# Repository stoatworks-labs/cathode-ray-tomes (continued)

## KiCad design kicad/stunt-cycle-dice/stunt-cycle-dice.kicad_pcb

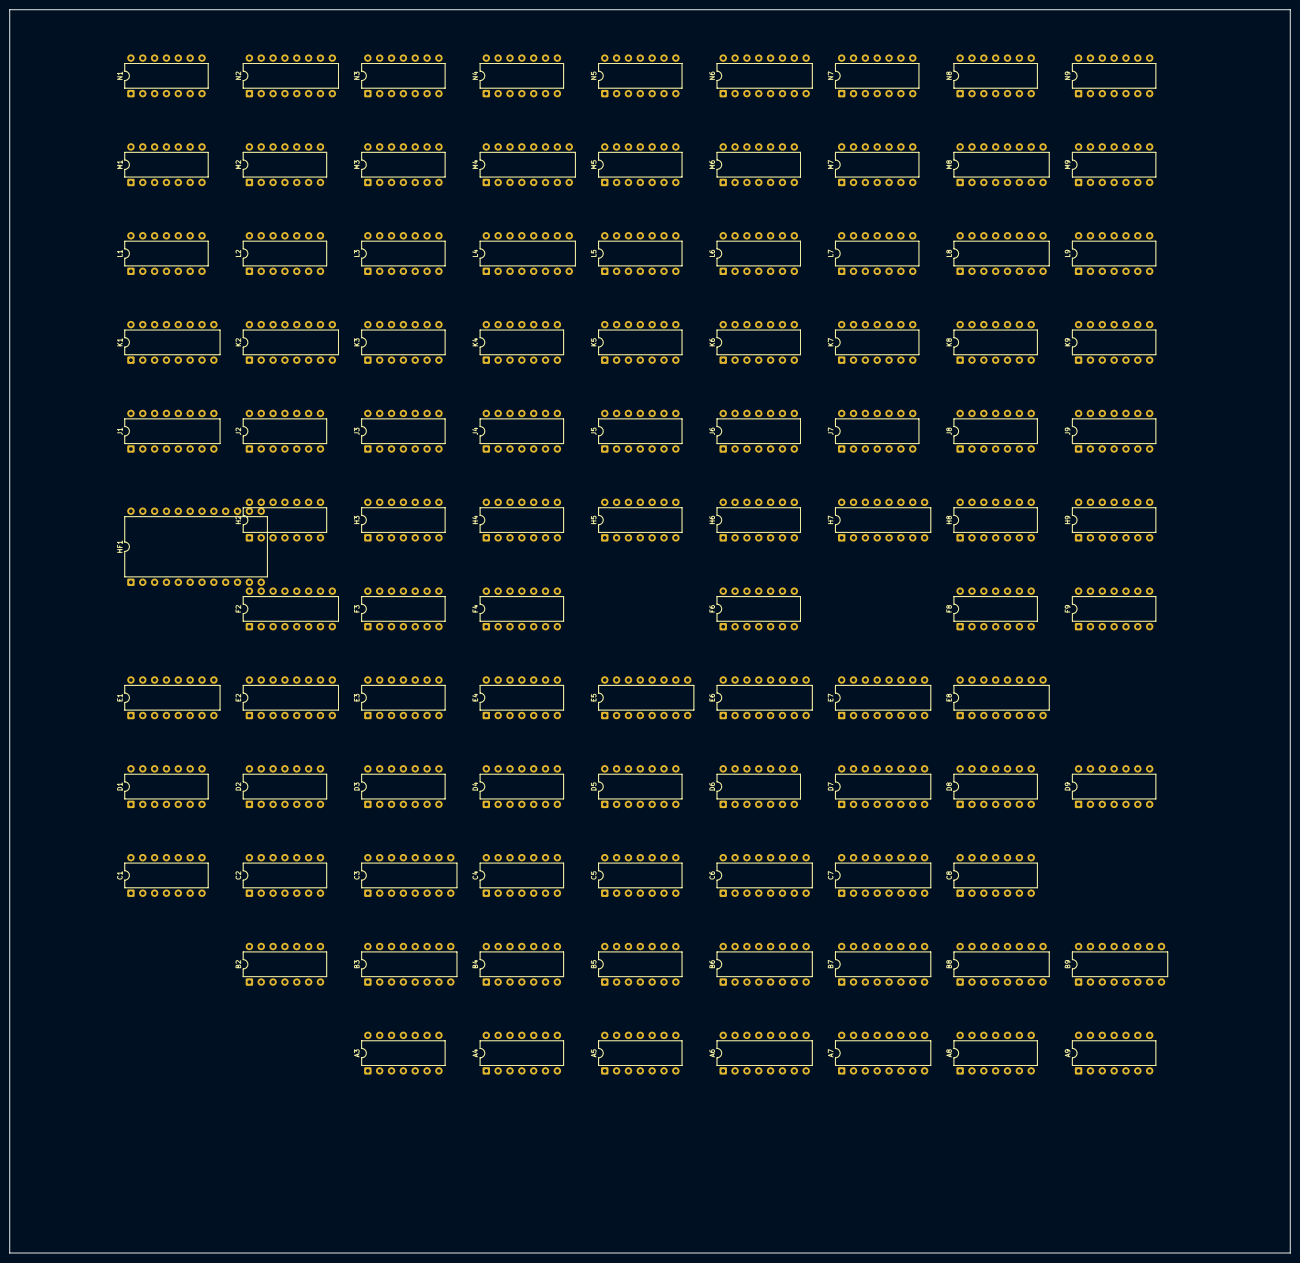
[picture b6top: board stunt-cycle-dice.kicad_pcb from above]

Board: 2 copper layers, 274.6 x 266.6 mm, 100 parts (0 on the bottom side), 328 nets, no tracks yet.

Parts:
A3: 7400; DIP-14_W7.62mm
A4, A5, A9: 7474; DIP-14_W7.62mm
A6: 9312; DIP-16_W7.62mm
A7: 9322; DIP-16_W7.62mm
A8: 7402; DIP-14_W7.62mm
B2: 7400; DIP-14_W7.62mm
B3: 9316; DIP-16_W7.62mm
B4: 74107; DIP-14_W7.62mm
B5: 7408; DIP-14_W7.62mm
B6: 9312; DIP-16_W7.62mm
B7: 9322; DIP-16_W7.62mm
B8, B9: 74192; DIP-16_W7.62mm
C1: 7493; DIP-14_W7.62mm
C2, C5: 7474; DIP-14_W7.62mm
C3: 9316; DIP-16_W7.62mm
C4: 7410; DIP-14_W7.62mm
C6: 7448; DIP-16_W7.62mm
C7: 9322; DIP-16_W7.62mm
C8: 7486; DIP-14_W7.62mm
D1: 7450; DIP-14_W7.62mm
D2, D9: 7474; DIP-14_W7.62mm
D3: 7404; DIP-14_W7.62mm
D4: 7402; DIP-14_W7.62mm
D5: 7400; DIP-14_W7.62mm
D6: 7410; DIP-14_W7.62mm
D7: 82S123; DIP-16_W7.62mm
D8: 7427; DIP-14_W7.62mm
E1, E2: 74194; DIP-16_W7.62mm
E3: 7410; DIP-14_W7.62mm
E4: 7427; DIP-14_W7.62mm
E5, E8: 74193; DIP-16_W7.62mm
E6, E7: 7485; DIP-16_W7.62mm
F2: 74165; DIP-16_W7.62mm
F3: 7450; DIP-14_W7.62mm
F4: 7400; DIP-14_W7.62mm
F6, F8: 7474; DIP-14_W7.62mm
F9: 7402; DIP-14_W7.62mm
H2: 7400; DIP-14_W7.62mm
H3, H8: 7474; DIP-14_W7.62mm
H4, H9: 7410; DIP-14_W7.62mm
H5: 7408; DIP-14_W7.62mm
H6: 7404; DIP-14_W7.62mm
H7: 9316; DIP-16_W7.62mm
HF1: 82S115; DIP-24_W15.24mm
J1: 9322; DIP-16_W7.62mm
J2, J7: 7474; DIP-14_W7.62mm
J3, J5: 7402; DIP-14_W7.62mm
J4: 7486; DIP-14_W7.62mm
J6: 7420; DIP-14_W7.62mm
J8: 7400; DIP-14_W7.62mm
J9: 74107; DIP-14_W7.62mm
K1, K2: 9316; DIP-16_W7.62mm
K3: 7493; DIP-14_W7.62mm
K4: 74107; DIP-14_W7.62mm
K5: 7427; DIP-14_W7.62mm
K6: 7402; DIP-14_W7.62mm
K7: 7474; DIP-14_W7.62mm
K8: 7404; DIP-14_W7.62mm
K9: 7450; DIP-14_W7.62mm
L1, L7: 7402; DIP-14_W7.62mm
L2, L9: 7400; DIP-14_W7.62mm
L3, L5: 7493; DIP-14_W7.62mm
L4: 9316; DIP-16_W7.62mm
L6: 7408; DIP-14_W7.62mm
L8: 74193; DIP-16_W7.62mm
M1, M3: 7474; DIP-14_W7.62mm
M2: 7486; DIP-14_W7.62mm
M4: 9316; DIP-16_W7.62mm
M5: 7410; DIP-14_W7.62mm
M6, M7: 7400; DIP-14_W7.62mm
M8: 74193; DIP-16_W7.62mm
M9: 7420; DIP-14_W7.62mm
N1: 7493; DIP-14_W7.62mm
N2: 7485; DIP-16_W7.62mm
N3: 7404; DIP-14_W7.62mm
N4, N7: 7474; DIP-14_W7.62mm
N5, N9: 7400; DIP-14_W7.62mm
N6: 9602; DIP-16_W7.62mm
N8: 7408; DIP-14_W7.62mm

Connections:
+5V: A3.14, A4.14, A5.14, A6.16, A7.16, A8.14, A9.14, B2.14, B3.16, B4.14, B5.14, B6.16, B7.16, B8.16, B9.16, C1.5, C2.14, C3.16, C4.14, C5.14, C6.16, C7.16, C8.14, D2.14, D3.14, D4.14, D5.14, D6.14, D7.16, D8.14, D9.14, E1.16, E2.16, E3.14, E4.14, E5.16, E6.16, E7.16, E8.16, F2.16, F4.14, F6.14, F8.14, F9.14, H2.14, H3.14, H4.14, H5.14, H6.14, H7.16, H8.14, H9.14, J1.16, J2.14, J3.14, J4.14, J5.14, J6.14, J7.14, J8.14, J9.14, K1.16, K2.16, K3.5, K4.14, K5.14, K6.14, K7.14, K8.14, L1.14, L2.14, L3.5, L4.16, L5.5, L6.14, L7.14, L8.16, L9.14, M1.14, M2.14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
A3-1: A3.1, C4.6
A3-3: A3.3, C4.3, C5.3
A3-4: A3.4, D3.12
A3-5: A3.5, B3.7, C3.15
A3-6: A3.6, B3.9, C2.11, C3.9
A4-8: A4.8, A8.12
A5-2: A5.2, B5.11
A5-6: A5.6, M7.5
A5-8: A5.8, J7.2
A5-11: A5.11, H5.2, H5.10, H6.1, H7.15, J7.13
A6-1: A6.1, C6.13
A6-4: A6.4, C6.14
A6-9: A6.9, C6.10
A6-14: A6.14, B5.12
A7-1: A7.1, B7.1, D1.8
A7-2: A7.2, A8.8, A9.9
A7-3: A7.3, A8.2, A9.5
A7-4: A7.4, C7.2, D7.14
A7-5: A7.5, A8.10
A7-6: A7.6, A8.1
A7-7: A7.7, C7.5
A8-3: A8.3, B7.10, B9.7
A8-4: A8.4, B8.5
A8-5: A8.5, B5.4, D5.12, D6.9, E5.3
A8-6: A8.6, C5.8
A8-9: A8.9, B7.11, B8.7
A8-13: A8.13, D3.9
A9-2: A9.2, A9.6
A9-3: A9.3, B9.12
A9-8: A9.8, A9.12
A9-11: A9.11, B8.12
ATTRACT: D9.8, D9.10, F3.2, F8.3, H8.3
ATTRACT_n: D8.13, D9.9, F3.1, F8.13, H5.12, H9.9, M5.4
B2-2: B2.2, B2.13, D3.8
B2-5: B2.5, C2.9, C3.3
B2-6: B2.6, C3.4
B3-15: B3.15, B4.9, C4.2
B4-2: B4.2, C4.1
B4-3: B4.3, C4.11
B4-5: B4.5, B4.12, C4.9, C4.13
B5-2: B5.2, B5.8, E4.1
B5-3: B5.3, D4.12
B5-5: B5.5, C5.9
B5-6: B5.6, B9.5
B5-13: B5.13, B6.14
B6-1: B6.1, C6.15
B6-4: B6.4, C6.12
B6-5: B6.5, C6.9
B6-9: B6.9, C6.11
B7-2: B7.2, B8.3
B7-3: B7.3, B9.3
B7-4: B7.4, C7.3, D7.10
B7-5: B7.5, B8.2
B7-6: B7.6, B9.2
B7-7: B7.7, C7.6, D7.11
B7-9: B7.9, C7.10, D7.13
B7-12: B7.12, C7.13, D7.12
B7-13: B7.13, B9.6
B7-14: B7.14, B8.6
BAD_JUMP: K7.9, L7.2, L7.12, L9.4, N6.4
BAD_JUMP_n: C4.4, F6.13, J7.1, K7.8, L9.2, L9.12, M7.10, M9.4, N9.9
C1-1: C1.1, C1.12
C1-14: C1.14, C2.5, C2.12
C2-1: C2.1, C2.8
C4-8: C4.8, E4.13
C4-12: C4.12, D3.13
C5-1: C5.1, D6.8
C5-6: C5.6, K6.8
C5-12: C5.12, D7.6, K6.5
C5-13: C5.13, H5.11
C6-1: C6.1, C7.7
C6-2: C6.2, C7.12
C6-6: C6.6, C7.9
C6-7: C6.7, C7.4
C8-4: C8.4, D6.12, D8.11
C8-5: C8.5, D7.5, K6.11
C8-6: C8.6, E6.3
C8-8: C8.8, D4.6, F4.9
C8-11: C8.11, E8.14, F9.12
CLOCK: A5.3, D2.3, F2.2, L4.2, M4.2, N4.9
CLOCK_n: F6.3, N4.8, N4.12
COMP_SCORE_n: A5.5, C5.4, K6.2
CYCLE: D2.8, F4.5, M5.13, M7.2
CYCLE_RESET: K8.3, L2.12, N6.10
CYCLE_RESET_A_n: A3.2, E1.1, E2.1, K7.1, K7.13, K8.4, N7.10
CYCLE_RESET_n: D5.5, L9.9, M3.1, N5.13, N6.3, N6.9, N7.1
CYCLE_WINDOW: L6.11, N8.1
CYCLE_n: D2.9, D4.3
D1-1: D1.1, D3.4
D1-2: D1.2, E1.15
D1-4: D1.4, E2.12
D1-6: D1.6, D2.12
D2-2: D2.2, F2.9, F2.10
D2-6: D2.6, E3.2
D2-11: D2.11, D3.10, E1.11, E2.11
D3-1: D3.1, D4.5, F4.11
D3-2: D3.2, F4.10
D3-5: D3.5, F3.6
D3-6: D3.6, E4.9
D4-1: D4.1, E4.11
D4-4: D4.4, E4.10
D4-10: D4.10, D4.11
D4-13: D4.13, H2.1
D5-2: D5.2, D5.6
D5-8: D5.8, E5.4
D5-9: D5.9, L6.2, M6.8
D5-10: D5.10, K6.10
D5-13: D5.13, H8.5, J8.12
D6-11: D6.11, H8.6, K9.10
D7-1: D7.1, E6.10, E7.10
D7-2: D7.2, E6.12, E7.12
D7-3: D7.3, E6.13, E7.13
D7-4: D7.4, E6.15, E7.15
D8-1: D8.1, J8.6, J9.8, J9.10, J9.13
D8-2: D8.2, F9.5, F9.6, F9.10
D8-3: D8.3, E8.2
D8-4: D8.4, E8.6
D8-5: D8.5, E8.7
D8-6: D8.6, K8.9
D8-12: D8.12, D9.4
D9-2: D9.2, F9.1
D9-13: D9.13, F9.13
DIRECTION: B2.12, D1.3, M3.5
DIRECTION_n: B2.1, B2.4, B5.1, D1.5, D4.8, M3.2, M3.6
E1-3: E1.3, F2.11, HF1.7
E1-4: E1.4, F2.12, HF1.8
E1-5: E1.5, F2.13, HF1.9
E1-6: E1.6, F2.14, HF1.10
E1-7: E1.7, E2.15
E1-12: E1.12, E2.2
E2-3: E2.3, F2.3, HF1.14
E2-4: E2.4, F2.4, HF1.15
E2-5: E2.5, F2.5, HF1.16
E2-6: E2.6, F2.6, HF1.17
E3-3: E3.3, F4.6
E3-4: E3.4, F4.8
E3-5: E3.5, F3.8
E3-6: E3.6, E4.5
E3-11: E3.11, L1.1, L2.5, M1.2
E3-13: E3.13, E4.8
E4-3: E4.3, F4.3
E5-13: E5.13, H6.13
E6-6: E6.6, F6.2
E7-3: E7.3, K6.13
E7-6: E7.6, H9.11
E8-3: E8.3, F9.8
E8-4: E8.4, J8.8
E8-5: E8.5, J8.2, J9.6
E8-11: E8.11, E8.12
F3-3: F3.3, F3.13, J3.4
F3-4: F3.4, F3.10, J3.10
F4-13: F4.13, K5.8
F6-6: F6.6, H5.9, H7.9
F6-8: F6.8, L6.10
F6-12: F6.12, L5.11, L6.9
F8-1: F8.1, H9.8
F8-2: F8.2, F8.8, J8.4
F8-4: F8.4, H8.8, J8.5
F8-9: F8.9, K9.9
F9-2: F9.2, H9.13
F9-3: F9.3, H9.5
F9-9: F9.9, H9.1, K8.8
F9-11: F9.11, H6.12
FIXED_RAMP_ZONE: D8.8, H6.3, L8.1, N5.4, N9.4
FIXED_RAMP_ZONE_n: D5.1, H5.1, H6.4, J7.11, L8.15
FLIP: C1.2, C1.3, L7.5, L7.9, M6.2, N7.5
FLIP_n: C4.5, L7.11, N7.4, N7.6
FREE_PLAY: F3.5, F8.6, F8.11
FREE_PLAY_n: F3.9, F8.5
GND: A3.7, A4.7, A5.7, A6.2, A6.3, A6.5, A6.6, A6.7, A6.8, A7.8, A7.10, A7.11, A7.13, A7.14, A7.15, A8.7, A9.7, B2.7, B3.3, B3.6, B3.8, B4.7, B5.7, B6.2, B6.3, B6.6, B6.7, B6.8, B7.8, B7.15, B8.1, B8.8, B8.10, B8.14, B8.15, B9.1, B9.8, B9.10, B9.14, B9.15, C1.10, C2.7, C3.8, C4.7, C5.2, C5.7, C6.8, C7.8, C7.11, C7.14, C7.15, C8.7, D2.7, D3.7, D4.7, D5.7, D6.7, D7.8, D7.15, D8.7, D9.7, E1.2, E1.8, E2.7, E2.8, E3.7, E4.7, E5.8, E5.14, E5.15, E6.2, E6.4, E6.8, E7.2, E7.4, E7.8, E8.8, F2.8, F2.15, F4.7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
GOOD_JUMP_n: C5.11, K7.6
GRAVITY: L6.8, L8.4, M9.2, M9.13
H1: C3.14, D3.11
H2: A4.11, C3.13
H2-3: H2.3, HF1.3
H2-6: H2.6, HF1.2
H2-8: H2.8, J3.6, J3.8
H2-9: H2.9, J3.13
H2-11: H2.11, H3.13
H3-4: H3.4, H3.8, J3.11, K6.6
H3-6: H3.6, H4.4
H4: A4.3, A4.12, A8.11, C3.11
H4-2: H4.2, L1.13
H4-11: H4.11, J4.11
H5: B3.14, B5.9, H2.5
H5-3: H5.3, L1.5, N1.2, N1.3
H5-6: H5.6, K1.10
H5-8: H5.8, M2.2, M2.5, M2.10, M2.13
H6: B3.13, B5.10, D4.9
H6-2: H6.2, H7.7
H7: B3.12, E4.2
H8: B3.11, C4.10
H8-1: H8.1, H9.6
H8-4: H8.4, H9.3, H9.12
H8-12: H8.12, H8.13, K8.10, K9.13
HCOUNTER_RESET_n: B3.1, B4.10, B4.13, C3.1, D5.3, D5.4
HF1-1: HF1.1, J1.4
HF1-21: HF1.21, J1.9
HF1-22: HF1.22, J1.12
HF1-23: HF1.23, J1.7
HF_CLOCK: B3.2, C3.2, N4.11
HRESET: H6.6, J5.6, L3.14, M3.11, M5.2
HRESET_n: A5.13, H6.5, J6.6, L4.9, M4.9
HSCORE_n: H4.8, J3.3
HSYNC: J1.1, J3.12, J5.1, J5.5, K1.2, K2.2, N4.2
HSYNC_n: F2.1, F6.11, H2.2, H2.4, J5.3, J5.4
HWINDOW: A4.2, E4.12, J7.3, N4.3, N5.5
HWINDOW_DELAYED: A4.5, A4.13, L6.12
J2-1: J2.1, J2.8, K2.10
J2-3: J2.3, M3.3, N4.5
J2-5: J2.5, J2.12
J2-9: J2.9, M6.9
J2-11: J2.11, N3.6
J7-5: J7.5, K7.2
J7-6: J7.6, K7.12
J8-1: J8.1, K9.8
J8-3: J8.3, J9.1
J8-10: J8.10, J8.11
J9-2: J9.2, J9.11
JUMP: L7.8, M6.10, M6.13, N9.2, N9.10, N9.11
JUMP_n: K7.3, K7.11, L8.14, M6.1, N9.3, N9.13
K1-3: K1.3, L8.3
K1-4: K1.4, L8.2
K1-5: K1.5, L8.6
K1-6: K1.6, K8.6
K1-9: K1.9, K2.9, L2.8
K1-15: K1.15, K2.7, L2.9
K6-4: K6.4, K6.9
K8-5: K8.5, L8.7
L1-2: L1.2, L2.3
L1-6: L1.6, M1.8
L2-4: L2.4, M1.4, M1.6
L2-11: L2.11, M1.1
L4-7: L4.7, M4.15
L5-1: L5.1, L5.12
L5-2: L5.2, L5.3, L7.1
L6-1: L6.1, M5.12
L6-3: L6.3, L6.4
L6-5: L6.5, M6.11
L6-6: L6.6, N6.11
L7-3: L7.3, L7.4
L7-6: L7.6, N8.3, N9.5
L7-13: L7.13, M6.12
L8-11: L8.11, N8.11, N9.12
L9-3: L9.3, M9.12
L9-6: L9.6, M9.9
L9-8: L9.8, M8.14
L9-10: L9.10, L9.11
L9-13: L9.13, M7.11
M1-12: M1.12, M2.8
M2-3: M2.3, N2.13
M2-6: M2.6, N2.10
M2-9: M2.9, N2.5
M2-11: M2.11, N2.12
M3-12: M3.12, M5.8
M5-1: M5.1, M7.8
M5-5: M5.5, N3.11, N5.11
M5-6: M5.6, M9.5, M9.10, N5.12
M6-3: M6.3, N6.5
M6-6: M6.6, N6.12
M7-13: M7.13, M8.13
M8-4: M8.4, M9.8
M8-5: M8.5, M9.6
M8-11: M8.11, N9.8
MS1: B2.11, E1.9, E2.9
MS2: B2.3, E1.10, E2.10
MS3: M7.9, M7.12, N7.8, N9.1
N1-1: N1.1, N1.12, N2.9
N1-8: N1.8, N2.14
N1-9: N1.9, N2.11
N1-11: N1.11, N2.1
N4-1: N4.1, N5.6
N4-4: N4.4, N4.6
N7-2: N7.2, N8.6
N8-13: N8.13, N9.6
OBJECT_HIT_n: K7.10, M7.3, N8.12
OBJECT_ZONE: D2.1, J7.9, M7.1
OBJECT_ZONE_n: J7.8, K6.12
PLAYER_CONTROL: C8.9, D4.2, F4.4, H6.8
PLAYER_CONTROL_n: D1.9, D5.11, H6.9
R2: HF1.4, M8.2, N8.4
R3: HF1.5, M8.6, N8.5
R4: C1.11, HF1.6
RAMPS: L1.4, L1.8, L1.9, N8.2
RAMPS_n: F4.1, L1.10
ROAD_n: F4.2, H4.6
SCORE1_n: E3.1, M7.6
SCORE2: E4.4, K6.1
SCORE_WINDOW: C6.4, J3.1
START: D9.6, D9.12, H9.2, H9.4, J8.9
START_n: A9.1, A9.13, B8.11, B9.11, D9.5, E5.11, M6.4
V1: J1.11, K1.14
V2: J1.14, K1.13
V3: J1.5, K1.12
V4: J1.2, K1.11
VCC: A4.1, A4.4, A4.10, A5.1, A5.4, A5.10, A5.12, A9.4, A9.10, B3.4, B3.5, B3.10, B4.1, B4.4, B4.8, B4.11, B8.4, B8.9, B9.4, B9.9, C2.2, C2.4, C2.10, C2.13, C3.5, C3.6, C3.7, C3.10, C5.10, C6.3, C8.13, D2.4, D2.13, D9.1, E5.5, E8.1, E8.9, E8.10, E8.15, F6.4, F6.10, F8.10, F8.12, H3.1, H3.10, H3.12, H7.1, H7.3, H7.4, H7.10, H8.10, HF1.18, J1.3, J2.2, J2.4, J2.10, J2.13, J7.4, J7.10, K1.7, K4.1, K4.4, K4.8, K4.11, K4.13, K7.4, L4.1, L4.10, L8.5, M1.10, M3.4, M3.10, M3.13, M4.1, M4.7, M4.10, M8.1, M8.15, N2.2, N2.3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
VCOUNTER_RESET_n: K1.1, K2.1, L2.6
VRAMP: J7.12, J8.13, M1.13, N3.8
VRAMP_n: E3.8, N3.9, N7.11
VRESET: D6.10, J5.12, K3.2, K3.3, L2.13, L3.2, L3.3, M3.8
VRESET_n: K4.10, L5.14, M3.9, N7.3
VSCORE_n: H4.12, J3.2, K5.11
VSYNC: J5.10, J5.11
VSYNC_n: H3.11, H5.5, J5.9, J5.13
VWINDOW: D2.10, K2.15, L2.10, L6.13, N7.12
_1H: H4.3, H7.2, M1.11, M4.14
_1V: H3.3, J1.10, L3.1, L3.12, M2.4, M5.11
_2H: B6.11, M4.13, N1.14
_2V: A6.11, J1.13, L3.9, M2.12, M5.10
_4H: B6.12, M4.12
_4V: A6.12, J1.6, L3.8, M2.1
_8H: A6.10, B6.10, E6.9, J6.1, M4.11
_8V: A6.13, B6.13, E3.9, H2.12, J5.8, K3.14, L3.11, M1.3
_16H: C6.5, C7.1, E6.11, L4.14
_16V: H4.1, K3.1, K3.12, L2.1
_32H: D8.10, E6.14, J4.4, J5.2, L4.13
_32H_xor_256H: H4.10, J4.6, K5.10
_32V: H2.13, H3.2, H4.5, H4.13, K3.9, L1.3, N3.5
_64H: D8.9, E6.1, J4.13, J6.2, K5.9, L4.12
_64V: H8.11, J9.9, J9.12, K3.8, L1.11, L2.2, L9.5
_128H: D6.2, D6.13, J4.10, J6.4, K4.12, K6.3, L4.11, M7.4
_128H_xor_256H: F4.12, F6.1, H2.10, H4.9, J4.8
_128V: D1.10, D3.3, E3.10, H5.13, K3.11, K4.9, L1.12
_256H: C8.10, J3.9, J4.5, J4.9, J6.5, K4.3
_256H_n: D1.13, D6.1, J3.5, J4.12, K4.2
_256V: D9.3, D9.11, K4.5, M5.9
_256V_n: H5.4, K4.6

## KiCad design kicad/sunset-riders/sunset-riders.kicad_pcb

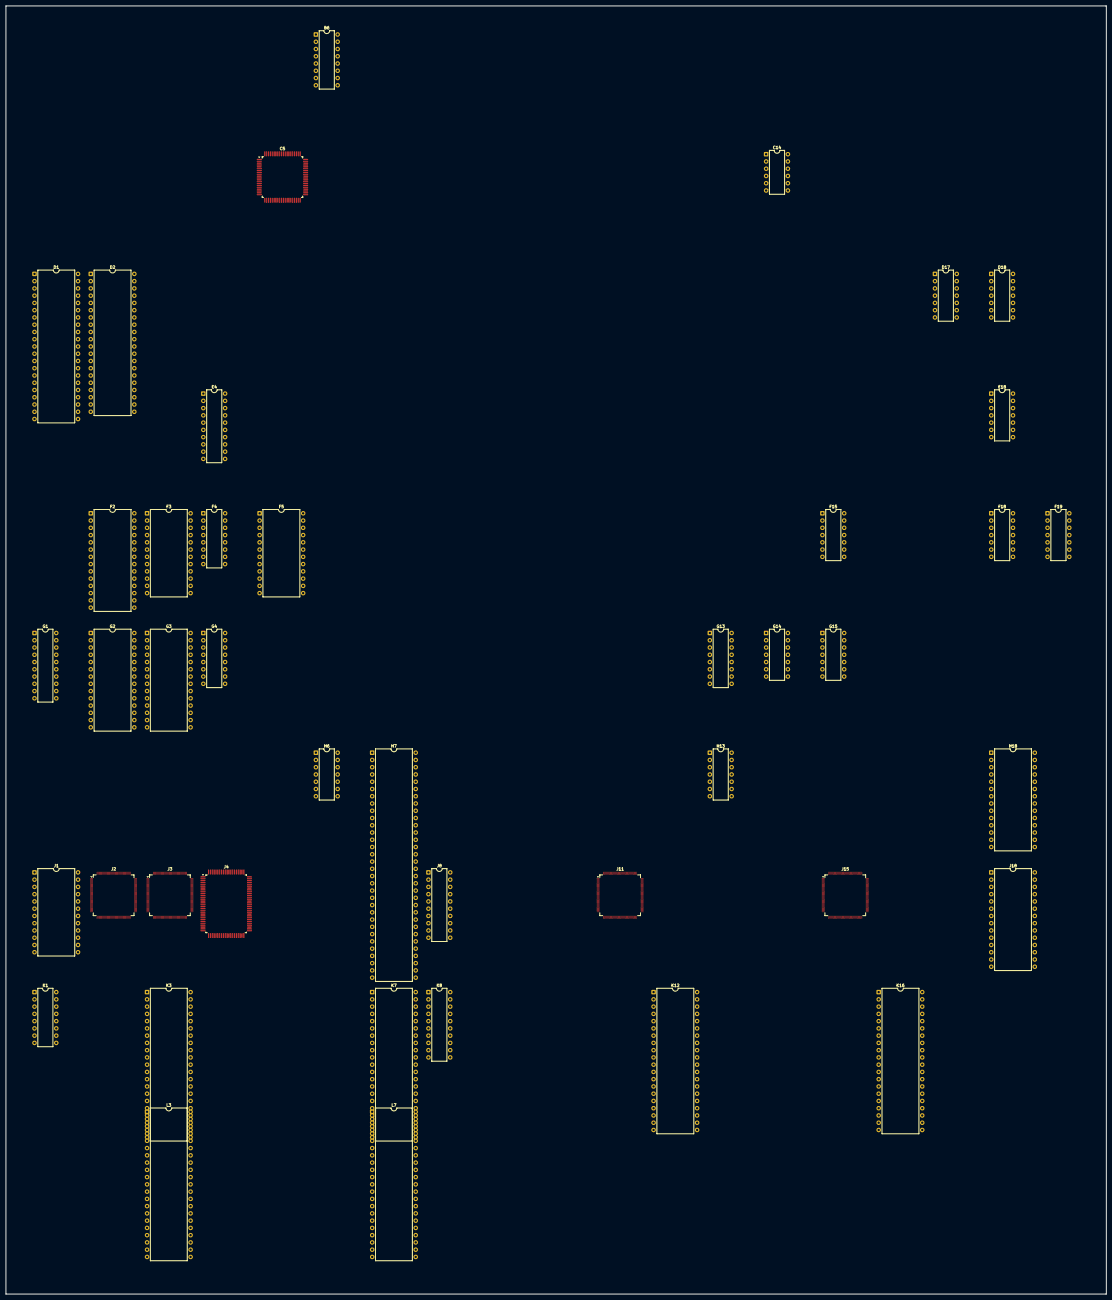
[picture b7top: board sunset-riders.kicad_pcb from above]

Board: 2 copper layers, 385.2 x 450.9 mm, 43 parts (0 on the bottom side), 412 nets, no tracks yet.

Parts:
B6: YM3012; DIP-16_W7.62mm
C5: 053260; PQFP-80_14x14mm_P0.65mm
C14: MB3722; DIP-12_W7.62mm
D1: 065A08; DIP-42_W15.24mm
D2: Z80CPU; DIP-40_W15.24mm
D17: 74LS00; DIP-14_W7.62mm
D18: 74LS32; DIP-14_W7.62mm
E4: PAL16L8; DIP-20_W7.62mm
E18: 74LS08; DIP-14_W7.62mm
F2: 27C512; DIP-28_W15.24mm
F3: CY7C128-45PC; DIP-24_W15.24mm
F4: 74LS157; DIP-16_W7.62mm
F5: PAL20RS10; DIP-24_W15.24mm
F15: 74LS74; DIP-14_W7.62mm
F18, F19: 74LS04; DIP-14_W7.62mm
G1: 74LS245; DIP-20_W7.62mm
G2, G3: MB8464A-80-10-15/L-LL; DIP-28_W15.24mm
G4: 74LS157; DIP-16_W7.62mm
G13: 74LS138; DIP-16_W7.62mm
G14: 74LS74; DIP-14_W7.62mm
G15: 74LS08; DIP-14_W7.62mm
H6: LM324; DIP-14_W7.62mm
H7: DIP-64_W15.24mm
H13: 74LS07; DIP-14_W7.62mm
H18: MB8464A-10W-15W; DIP-28_W15.24mm
J1: HM6116P-3; DIP-24_W15.24mm
J2: 053245; TQFP-120_14x14mm_P0.4mm
J3: 053244; TQFP-120_14x14mm_P0.4mm
J4: 053251; PQFP-100_14x20mm_P0.65mm
J8: 74LS245; DIP-20_W7.62mm
J11: 051962; TQFP-120_14x14mm_P0.4mm
J15: 052109; TQFP-120_14x14mm_P0.4mm
J18: MB8464A-10W-15W; DIP-28_W15.24mm
K1: 74LS367; DIP-16_W7.62mm
K3, K7: 065A08; DIP-42_W15.24mm
K8: 74LS245; DIP-20_W7.62mm
K12, K16: 955D05-06-07-08; DIP-40_W15.24mm
L3, L7: 065A08; DIP-42_W15.24mm

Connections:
/D0: H7.31, K8.18
/D1: H7.32, K8.17
/D2: H7.33, K8.16
/D3: H7.35, K8.15
/D4: H7.36, K8.14
/D5: H7.37, K8.13
/D6: H7.38, K8.12
/D7: H7.39, K8.11
/D8: H7.40, J8.18
/D9: H7.43, J8.17
/D10: H7.44, J8.16
/D11: H7.45, J8.15
/D12: H7.46, J8.14
/D13: H7.47, J8.13
/D14: H7.48, J8.12
/D15: H7.49, J8.11
/IO: F5.18, G13.5
/M6: J2.10, J3.10, J4.41, J11.78
/M12: J2.12, J3.12, J11.95
/MAIN_A1: G4.2, G15.2, H7.30, J4.85, J11.88, J15.66
/MAIN_A2: G4.5, H7.29, J2.25, J3.18, J4.84, J11.89, J15.67
/MAIN_A3: G4.11, H7.28, J2.24, J3.17, J4.83, J15.68
/MAIN_A4: G4.14, H7.27, J2.23, J3.15, J4.82, J15.69
/MAIN_A5: F4.2, G15.5, H7.24, J15.116
/MAIN_A6: F4.5, G15.10, H7.23, J15.115
/MAIN_A7: H7.22, J2.22, J15.114
/MAIN_A8: G13.1, H7.21, J2.20, J15.113
/MAIN_A9: G13.2, H7.20, J2.19, J15.112
/MAIN_A10: G13.3, H7.19, J2.18, J15.111
/MAIN_A11: E18.9, G13.4, H7.17, J2.17, J15.110
/MAIN_A12: H7.16, J2.15, J15.109
/MAIN_A13: H7.15, J2.14, J15.80
/MAIN_A15: H7.13, J15.82
/MAIN_A21: F5.8, H7.5
/MAIN_A22: F5.7, H7.4
/MRW: D18.2, E18.12
/M~RD: F4.11, G1.1, J2.13, J3.20, J11.87, J15.85
/OBJ~SET: D17.1, E18.13, J2.6, J3.13
/PDB0: C5.8, J3.29, J4.80, J11.79, J15.56
/PDB1: C5.9, J3.28, J4.79, J11.80, J15.57
/PDB2: C5.10, J3.27, J4.77, J11.81, J15.58
/PDB3: C5.11, J3.26, J4.76, J11.82, J15.59
/PDB4: C5.13, J3.25, J4.75, J11.83, J15.60
/PDB5: C5.14, J3.24, J4.74, J11.84, J15.62
/PDB6: C5.15, J3.23, J15.63
/PDB7: C5.16, J3.22, J11.86, J15.64
/PDS: E18.10, F15.4, G13.6
/RM~RD: J11.96, J15.97
/SCR~CLK: J11.90, J15.65
/colmix/ACOL0: J4.57, J11.30
/colmix/ACOL1: J4.58, J11.32
/colmix/ACOL2: J4.59, J11.33
/colmix/ACOL3: J4.60, J11.34
/colmix/APAL0: J4.61, J11.36
/colmix/APAL1: J4.62, J11.37
/colmix/APAL2: J4.63, J11.38
/colmix/BCOL0: J4.66, J11.46
/colmix/BCOL1: J4.67, J11.47
/colmix/BCOL2: J4.68, J11.48
/colmix/BCOL3: J4.69, J11.49
/colmix/BPAL0: J4.70, J11.51
/colmix/BPAL1: J4.71, J11.52
/colmix/BPAL2: J4.72, J11.53
/colmix/FCOL0: J4.47, J11.59
/colmix/FCOL1: J4.48, J11.60
/colmix/FCOL2: J4.49, J11.62
/colmix/FCOL3: J4.50, J11.63
/colmix/FPAL0: J4.51, J11.65
/colmix/FPAL1: J4.52, J11.66
/colmix/OCOL0: J3.120, J4.30
/colmix/OCOL1: J3.119, J4.31
/colmix/OCOL2: J3.118, J4.32
/colmix/OCOL3: J3.117, J4.33
/colmix/OCOL4: J3.116, J4.34
/colmix/OCOL5: J3.115, J4.35
/colmix/OCOL6: J3.114, J4.36
/colmix/OCOL7: J3.113, J4.37
/colmix/OCOL8: J3.112, J4.38
/colmix/PCU~CS: G13.7, J4.81
/colmix/PR13: J3.110, J4.25
/colmix/PR14: J3.109, J4.27
/colmix/SDI0: J3.108, J4.95
/objects/AR0: J2.119, J3.30
/objects/AR1: J2.118, J3.32
/objects/AR2: J2.117, J3.33
/objects/AROK: J2.116, J3.34
/objects/BK0: G1.18, J1.9, K1.3, K3.36, K7.36, L3.36, L7.36
/objects/BK1: G1.17, J1.10, K1.5, K3.35, K7.35, L3.35, L7.35
/objects/BK2: G1.16, J1.11, K1.7, K3.34, K7.34, L3.34, L7.34
/objects/BK3: G1.15, J1.13, K1.9, K3.33, K7.33, L3.33, L7.33
/objects/BK4: G1.14, J1.14, K1.11, K3.2, K7.2, L3.2, L7.2
/objects/BK5: G1.13, J1.15, K1.13, K3.1, K7.1, L3.1, L7.1
/objects/BK6: G1.12, J1.16
/objects/BK7: G1.11, J1.17
/objects/BR0: J2.115, J3.35
/objects/BR1: J2.114, J3.36
/objects/BR2: J2.113, J3.37
/objects/BROK: J2.112, J3.38
/objects/CLAT: J2.86, J3.64
/objects/HP0: J2.96, J3.54
/objects/HP1: J2.97, J3.53
/objects/HP2: J2.98, J3.52
/objects/HP3: J2.99, J3.50
/objects/HP4: J2.100, J3.49
/objects/HP5: J2.102, J3.48
/objects/HP6: J2.103, J3.47
/objects/HP7: J2.104, J3.45
/objects/HP8: J2.105, J3.44
/objects/HP9: J2.107, J3.43
/objects/HRFP: J2.110, J3.39
/objects/OBJMPX: D17.9, F5.5, G15.1, G15.4, G15.9
/objects/OBJROMA0: J2.85, K3.10, K7.10, L3.10, L7.10
/objects/OBJROMA1: J2.84, K3.9, K7.9, L3.9, L7.9
/objects/OBJROMA2: J2.83, K3.8, K7.8, L3.8, L7.8
/objects/OBJROMA3: J2.82, K3.7, K7.7, L3.7, L7.7
/objects/OBJROMA4: J2.80, K3.6, K7.6, L3.6, L7.6
/objects/OBJROMA5: J2.79, K3.5, K7.5, L3.5, L7.5
/objects/OBJROMA6: J2.78, K3.4, K7.4, L3.4, L7.4
/objects/OBJROMA7: J2.77, K3.3, K7.3, L3.3, L7.3
/objects/OBJROMA8: J2.75, K3.41, K7.41, L3.41, L7.41
/objects/OBJROMA9: J2.74, K3.40, K7.40, L3.40, L7.40
/objects/OBJROMA10: J2.73, K3.39, K7.39, L3.39, L7.39
/objects/OBJROMA11: J2.72, K3.38, K7.38, L3.38, L7.38
/objects/OBJROMA12: J2.70, K3.37, K7.37, L3.37, L7.37
/objects/OBJROMA13: G4.3, J2.69, K1.2
/objects/OBJROMA14: G4.6, J2.68, K1.4
/objects/OBJROMA15: G4.10, J2.67, K1.6
/objects/OBJROMA16: G4.13, J2.66, K1.10
/objects/OBJROMA17: F4.3, J2.65, K1.12
/objects/OBJROMA18: F4.6, J2.64, K1.14
/objects/OBJROMD0: J3.100, K7.14, L7.14
/objects/OBJROMD1: J3.99, K7.16, L7.16
/objects/OBJROMD2: J3.98, K7.18, L7.18
/objects/OBJROMD3: J3.97, K7.20, L7.20
/objects/OBJROMD4: J3.96, K7.23, L7.23
/objects/OBJROMD5: J3.95, K7.25, L7.25
/objects/OBJROMD6: J3.94, K7.27, L7.27
/objects/OBJROMD7: J3.93, K7.29, L7.29
/objects/OBJROMD8: J3.92, K7.15, L7.15
/objects/OBJROMD9: J3.90, K7.17, L7.17
/objects/OBJROMD10: J3.89, K7.19, L7.19
/objects/OBJROMD11: J3.88, K7.21, L7.21
/objects/OBJROMD12: J3.87, K7.24, L7.24
/objects/OBJROMD13: J3.86, K7.26, L7.26
/objects/OBJROMD14: J3.85, K7.28, L7.28
/objects/OBJROMD15: J3.84, K7.30, L7.30
/objects/OBJROMD16: J3.83, K3.14, L3.14
/objects/OBJROMD17: J3.82, K3.16, L3.16
/objects/OBJROMD18: J3.80, K3.18, L3.18
/objects/OBJROMD19: J3.79, K3.20, L3.20
/objects/OBJROMD20: J3.78, K3.23, L3.23
/objects/OBJROMD21: J3.77, K3.25, L3.25
/objects/OBJROMD22: J3.75, K3.27, L3.27
/objects/OBJROMD23: J3.74, K3.29, L3.29
/objects/OBJROMD24: J3.73, K3.15, L3.15
/objects/OBJROMD25: J3.72, K3.17, L3.17
/objects/OBJROMD26: J3.70, K3.19, L3.19
/objects/OBJROMD27: J3.69, K3.21, L3.21
/objects/OBJROMD28: J3.68, K3.24, L3.24
/objects/OBJROMD29: J3.67, K3.26, L3.26
/objects/OBJROMD30: J3.66, K3.28, L3.28
/objects/OBJROMD31: J3.65, K3.30, L3.30
/objects/PL0: J2.87, J3.63
/objects/PL1: J2.88, J3.62
/objects/PL2: J2.89, J3.60
/objects/PL3: J2.90, J3.59
/objects/PL4: J2.92, J3.58
/objects/PL5: J2.93, J3.57
/objects/PL6: J2.94, J3.56
/objects/RA0: G2.10, G3.10, G15.3
/objects/RA1: G2.9, G3.9, J2.52
/objects/RA2: G2.8, G3.8, J2.53
/objects/RA3: G2.7, G3.7, J2.54
/objects/RA4: G2.6, G3.6, G15.6
/objects/RA5: G2.5, G3.5, G15.8
/objects/RA6: G2.4, G3.4, J2.55
/objects/RA7: G2.3, G3.3, J2.56
/objects/RA8: G2.25, G3.25, J2.57
/objects/RA9: G2.24, G3.24, J2.58
/objects/RA10: G2.21, G3.21, J2.59
/objects/RA11: G2.23, G3.23, J2.62
/objects/RA12: G2.2, G3.2, J2.63
/objects/RD0: G3.11, J2.45, K8.2
/objects/RD1: G3.12, J2.44, K8.3
/objects/RD2: G3.13, J2.43, K8.4
/objects/RD3: G3.15, J2.42, K8.5
/objects/RD4: G3.16, J2.40, K8.6
/objects/RD5: G3.17, J2.39, K8.7
/objects/RD6: G3.18, J2.38, K8.8
/objects/RD7: G3.19, J2.37, K8.9
/objects/RD8: G2.19, J2.35, J8.2
/objects/RD9: G2.18, J2.34, J8.3
/objects/RD10: G2.17, J2.33, J8.4
/objects/RD11: G2.16, J2.32, J8.5
/objects/RD12: G2.15, J2.30, J8.6
/objects/RD13: G2.13, J2.29, J8.7
/objects/RD14: G2.12, J2.28, J8.8
/objects/RD15: G2.11, J2.27, J8.9
/objects/R~OE: G2.22, G3.22, J2.49
/objects/SHADOW: J2.95, J3.55
/objects/~HIT: J2.108, J3.42
/objects/~WE1: G2.27, J2.48
/objects/~WE2: G3.27, J2.47
/objects/~ZLD: J2.109, J3.40
/pcm_snd/AUX2: C5.24, D1.13
/pcm_snd/PCM~CS: C5.72, E4.19
/pcm_snd/RA0: C5.39, D1.30
/pcm_snd/RA1: C5.40, D1.10
/pcm_snd/RA2: C5.41, D1.9
/pcm_snd/RA3: C5.42, D1.8
/pcm_snd/RA4: C5.44, D1.7
/pcm_snd/RA5: C5.45, D1.6
/pcm_snd/RA6: C5.46, D1.5
/pcm_snd/RA8: C5.48, D1.3
/pcm_snd/RA9: C5.49, D1.41
/pcm_snd/RA10: C5.50, D1.40
/pcm_snd/RA11: C5.51, D1.39
/pcm_snd/RA12: C5.53, D1.38
/pcm_snd/RA13: C5.54, D1.37
/pcm_snd/RA14: C5.55, D1.36
/pcm_snd/RA15: C5.56, D1.35
/pcm_snd/RA16: C5.57, D1.34
/pcm_snd/RA17: C5.58, D1.33
/pcm_snd/RA20: C5.62, D1.42
/pcm_snd/RD0: C5.29, D1.14
/pcm_snd/RD1: C5.30, D1.16
/pcm_snd/RD2: C5.31, D1.18
/pcm_snd/RD3: C5.32, D1.20
/pcm_snd/RD4: C5.35, D1.23
/pcm_snd/RD5: C5.36, D1.25
/pcm_snd/RD6: C5.37, D1.27
/pcm_snd/RD7: C5.38, D1.29
/pcm_snd/SH1: B6.6, C5.26, F5.11
/pcm_snd/SH2: B6.5, C5.27
/pcm_snd/SND_A0: C5.70, D2.30, F2.10, F3.8
/pcm_snd/SND_A1: C5.69, D2.31, F2.9, F3.7
/pcm_snd/SND_A2: C5.68, D2.32, F2.8, F3.6
/pcm_snd/SND_A3: C5.67, D2.33, F2.7, F3.5
/pcm_snd/SND_A4: C5.66, D2.34, F2.6, F3.4
/pcm_snd/SND_A5: C5.65, D2.35, F2.5, F3.3
/pcm_snd/SND_D0: C5.5, F2.11, F3.9
/pcm_snd/SND_D1: C5.4, F2.12, F3.10
/pcm_snd/SND_D2: C5.3, D2.12, F2.13, F3.11
/pcm_snd/SND_D3: C5.2, D2.8, D2.14, F2.15, F3.13
/pcm_snd/SND_D4: C5.1, D2.15, F2.16, F3.14
/pcm_snd/SND_D5: C5.80, D2.9, F2.17, F3.15
/pcm_snd/SND_D6: C5.79, D2.10, F2.18, F3.16
/pcm_snd/SND_D7: C5.78, D2.13, D2.18, F2.19, F3.17
/pcm_snd/SY: B6.2, C5.25
/scroll/COL5: J11.109, J15.42
/scroll/COL6: J11.108, J15.43
/scroll/COL7: J11.107, J15.46
/scroll/GFXROMA0: J15.35, K12.9, K16.9
/scroll/GFXROMA1: J15.34, K12.8, K16.8
/scroll/GFXROMA2: J15.33, K12.7, K16.7
/scroll/GFXROMA3: J15.32, K12.6, K16.6
/scroll/GFXROMA4: J15.30, K12.5, K16.5
/scroll/GFXROMA5: J15.29, K12.4, K16.4
/scroll/GFXROMA6: J15.28, K12.3, K16.3
/scroll/GFXROMA7: J15.27, K12.2, K16.2
/scroll/GFXROMA8: J15.26, K12.40, K16.40
/scroll/GFXROMA9: J15.25, K12.39, K16.39
/scroll/GFXROMA10: J15.24, K12.38, K16.38
/scroll/GFXROMA11: J15.37, K12.37, K16.37
/scroll/GFXROMA12: J15.38, K12.36, K16.36
/scroll/GFXROMA13: J15.41, K12.35, K16.35
/scroll/GFXROMA14: J15.39, K12.34, K16.34
/scroll/GFXROMA15: J15.40, K12.33, K16.33
/scroll/GFXROMA16: J15.23, K12.32, K16.32
/scroll/GFXROMA17: J15.22, K12.1, K16.1
/scroll/GFXROMD0: J11.29, K16.13
/scroll/GFXROMD1: J11.28, K16.15
/scroll/GFXROMD2: J11.27, K16.17
/scroll/GFXROMD3: J11.26, K16.19
/scroll/GFXROMD4: J11.25, K16.22
/scroll/GFXROMD5: J11.24, K16.24
/scroll/GFXROMD6: J11.23, K16.26
/scroll/GFXROMD7: J11.22, K16.28
/scroll/GFXROMD8: J11.21, K16.14
/scroll/GFXROMD9: J11.20, K16.16
/scroll/GFXROMD10: J11.19, K16.18
/scroll/GFXROMD11: J11.18, K16.20
/scroll/GFXROMD12: J11.17, K16.23
/scroll/GFXROMD13: J11.16, K16.25
/scroll/GFXROMD14: J11.13, K16.27
/scroll/GFXROMD15: J11.12, K16.29
/scroll/GFXROMD16: J11.11, K12.13
/scroll/GFXROMD17: J11.10, K12.15
/scroll/GFXROMD18: J11.9, K12.17
/scroll/GFXROMD19: J11.8, K12.19
/scroll/GFXROMD20: J11.7, K12.22
/scroll/GFXROMD21: J11.6, K12.24
/scroll/GFXROMD22: J11.5, K12.26
/scroll/GFXROMD23: J11.4, K12.28
/scroll/GFXROMD24: J11.3, K12.14
/scroll/GFXROMD25: J11.2, K12.16
/scroll/GFXROMD26: J11.120, K12.18
/scroll/GFXROMD27: J11.119, K12.20
/scroll/GFXROMD28: J11.118, K12.23
/scroll/GFXROMD29: J11.117, K12.25
/scroll/GFXROMD30: J11.116, K12.27
/scroll/GFXROMD31: J11.115, K12.29
/scroll/SCRAMA0: H18.10, J15.2, J18.10
/scroll/SCRAMA1: H18.9, J15.120, J18.9
/scroll/SCRAMA2: H18.8, J15.119, J18.8
/scroll/SCRAMA3: H18.7, J15.118, J18.7
/scroll/SCRAMA4: H18.6, J15.117, J18.6
/scroll/SCRAMA5: H18.5, J15.70, J18.5
/scroll/SCRAMA6: H18.4, J15.71, J18.4
/scroll/SCRAMA7: H18.3, J15.72, J18.3
/scroll/SCRAMA8: H18.25, J15.73, J18.25
/scroll/SCRAMA9: H18.24, J15.76, J18.24
/scroll/SCRAMA10: H18.21, J15.77, J18.21
/scroll/SCRAMA11: H18.23, J15.78, J18.23
/scroll/SCRAMA12: H18.2, J15.79, J18.2
/scroll/VD0: H18.11, J15.20
/scroll/VD1: H18.12, J15.19
/scroll/VD2: H18.13, J15.18
/scroll/VD3: H18.15, J15.17
/scroll/VD4: H18.16, J15.16
/scroll/VD5: H18.17, J15.13
/scroll/VD6: H18.18, J15.12
/scroll/VD7: H18.19, J15.11
/scroll/VD8: J15.10, J18.11
/scroll/VD9: J15.9, J18.12
/scroll/VD10: J15.8, J18.13
/scroll/VD11: J15.7, J18.15
/scroll/VD12: J15.6, J18.16
/scroll/VD13: J15.5, J18.17
/scroll/VD14: J15.4, J18.18
/scroll/VD15: J15.3, J18.19
/scroll/ZA1H: J11.101, J15.50
/scroll/ZA2H: J11.100, J15.51
/scroll/ZA4H: J11.99, J15.52
/scroll/ZB1H: J11.106, J15.47
/scroll/ZB2H: J11.103, J15.48
/scroll/ZB4H: J11.102, J15.49
/scroll/~BE: J11.98, J15.53
/scroll/~RCS1: J15.93, J18.20
/scroll/~ROE1: J15.95, J18.22
/scroll/~ROE2: H18.22, J15.96
/scroll/~RWE1: J15.107, J18.27
/scroll/~RWE2: H18.27, J15.108
/sound/ROM~OE: E4.16, F2.22
/sound/SND_A6: D2.36, F2.4, F3.2
/sound/SND_A7: D2.37, F2.3, F3.1
/sound/SND_A8: D2.38, F2.25, F3.23
/sound/SND_A9: D2.39, E4.14, F2.24, F3.22
/sound/SND_A10: D2.40, E4.13, F2.21, F3.19
/sound/SND_A11: E4.11, F2.23
/sound/SND_A12: D2.2, E4.9, F2.2
/sound/SND_A13: E4.8, F2.26
/sound/SND_A14: D2.4, E4.7, F2.27
/sound/SND_A15: E4.6, F2.1
/sound/SRAM~CE: E4.17, F3.18
/sound/S~CLK: G14.5, G14.11
/sound/S~IORQ: D2.20, G15.13
/sound/S~MREQ: D2.19, E4.1
/sound/S~RD: D2.6, D2.21, E4.4, F3.20, F19.3
/sound/S~WR: D2.5, E4.5, F3.21
/sound/~M1: D2.27, E4.3
/sound/~NMI_CLR: E4.12, F5.10
/sound/~RFSH: D2.28, E4.2
/sound/~WAIT: D2.24, G14.9
/sound/~WSET: E4.15, G14.10
/~HSYNC: J2.4, J3.8, J11.73
/~LDS: E18.2, H7.63, J2.9
/~OBJ: D17.2, D18.1, F5.21
/~OVRC: F4.1, G1.19, G4.1, G13.10
/~RESET: J2.3, J3.3, J11.92, J15.55
/~SYSRES: B6.7, C5.75, D2.3, D2.26, F5.13, G15.12, H7.59, H13.8
/~UDS: E18.1, H7.62, J2.8, J3.19, J15.81
/~VRAM: J11.97, J15.54, J15.84
/~VSYNC: J2.5, J3.9, J11.72
GND: E4.10, F15.2
unnamed: B6.14, H6.2
unnamed: B6.12, H6.10
unnamed: B6.9, H6.5
unnamed: B6.10, H6.12
unnamed: B6.13, H6.1
unnamed: B6.15, H6.3
unnamed: C5.71, F19.4
unnamed: D2.7, E4.18
unnamed: D2.16, F5.6
unnamed: D2.17, F5.9
unnamed: D17.4, F19.12
unnamed: D17.5, E18.8
unnamed: D17.3, D17.10
unnamed: F4.4, J1.4
unnamed: F4.7, J1.3
unnamed: F4.9, J1.20
unnamed: F4.12, J1.21
unnamed: F5.1, G15.11
unnamed: G4.4, J1.8
unnamed: G4.7, J1.7
unnamed: G4.9, J1.6
unnamed: G4.12, J1.5
unnamed: G14.2, G14.6
unnamed: G14.8, G14.12
unnamed: H6.6, H6.7
unnamed: H6.8, H6.9
unnamed: H6.13, H6.14
unnamed: D17.6, H7.54
unnamed: F19.13, J2.26
unnamed: D18.3, J2.7
unnamed: E18.3, J3.14
unnamed: E18.11, J8.1, K8.1
unnamed: D17.8, J8.19, K8.19
unnamed: H13.9, J15.98
unnamed: F18.8, K3.13
VCC: B6.1, C5.20, C5.33, C5.73, D1.4, D1.11, D1.22, D1.31, D2.22, E4.20, F2.28, F3.24, F4.13, F5.2, F5.4, F5.24, F15.1, G2.26, G2.28, G3.26, G3.28, G14.1, G14.4, G14.13, H7.9, H7.26, H7.41, H7.58, H18.26, H18.28, J1.24, J2.16, J2.46, J2.60, J2.76, J2.106, J2.120, J3.16, J3.46, J3.76, J3.106, J4.1, J4.2, J4.3, J4.28, J4.29, J4.39, J4.42, J4.43, J4.44, J4.45, J4.46, J4.53, J4.78, J4.97, J4.98, J4.99, J4.100, J11.14, J11.44, J11.74, J11.104, J15.14, J15.44, J15.74, J15.104, J18.26, J18.28, K1.16, K3.22, K3.31, K3.32, K7.22, K7.31, K7.32, K12.21, K12.31, K16.21, K16.31, L3.22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
VSS: B6.3, B6.8, B6.16, C5.12, C5.34, C5.43, C5.52, C5.61, C5.74, C14.6, C14.7, D1.1, D1.2, D1.12, D1.32, D2.1, D2.11, D2.29, F2.14, F2.20, F3.12, F4.10, F4.15, F5.12, F18.9, G2.14, G2.20, G3.14, G3.20, G4.15, H7.2, H7.10, H7.18, H7.25, H7.34, H7.42, H7.50, H7.55, H7.57, H18.14, H18.20, J1.12, J1.18, J1.19, J1.22, J2.1, J2.2, J2.11, J2.21, J2.31, J2.41, J2.51, J2.61, J2.71, J2.81, J2.91, J2.101, J2.111, J3.1, J3.2, J3.4, J3.5, J3.6, J3.7, J3.11, J3.21, J3.31, J3.41, J3.51, J3.61, J3.71, J3.81, J3.91, J3.101, J3.111, J4.4, J4.5, J4.6, J4.7, J4.8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

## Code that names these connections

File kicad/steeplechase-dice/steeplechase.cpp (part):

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    * Signals                                                                 *
	**************************************************************************/
    #define CLOCK           "K1", 5
    #define CLOCK_n         "K1", 5
    #define BUFFERED_CLOCK  "L1", 12
    
    #define HCLOCK1 "M1", 10
    #define HCLOCK2 "M1", 2
    #define HCLOCK3 "M1", 4
    #define HCLOCK4 "M1", 12

    #define H1      "H2", 5
    #define H2      "H1", 14
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    #define H64     "F1", 13
    #define H128    "F1", 12
    #define H256    "F1", 11
    #define H256_n  "L1", 8

    #define HRESET_n "D1", 6
    #define HBLANK_n "H2", 9
    #define HSYNC    "J2", 10

    #define V1      "C2", 5
    #define V1_n    "C2", 6
    #define V2      "C3", 14
    #define V4      "C3", 13
    #define V8      "C3", 12
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    #define V64     "D3", 13
    #define V128    "D3", 12
    #define V256    "D3", 11
    #define V256_n  "D2", 10

    //#define VRESET   "D3", 15
    #define VRESET   "BUF1", 2
    #define VRESET_n "D2", 12
    #define VBLANK_n "E3", 5
    #define VSYNC    "J2", 13
    #define VF1      "E3", 9

    #define TRACK            "C3", 15
    #define TRACK_CLOCK      "D2", 6
    #define TRACK_CLOCK_n    "D1", 3
    #define HALF_TRACK_CLOCK "D2", 4

    #define F1   "H3", 14
    #define F2   "H3", 13
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    #define F8   "H3", 11
    #define F16  "B7", 5

    #define FWD1 "K3", 12
    #define FWD2 "K3", 4
    #define FWD3 "K3", 10
    #define FWD4 "K3", 6
    #define FWD5 "K3", 8
    #define FWD6 "K3", 2
    #define FWD7_n "J1", 3

    #define REV1 "J6", 6
    #define REV2 "J7", 6
    #define REV3 "J6", 12
    #define REV4 "J7", 12
    #define REV5 "J7", 8
    #define REV6 "J6", 8

    #define JUMP1 "H6", 10
    #define JUMP2 "H7", 10
    #define JUMP3 "H6", 1
    #define JUMP4 "H7", 1
    #define JUMP5 "H7", 4
    #define JUMP6 "H6", 4
    #define JUMP7 "J4", 5

    #define FALL1 "L5", 5
    #define FALL2 "L5", 9
    #define FALL3 "K5", 5
    #define FALL4 "K5", 9
    #define FALL5 "M5", 9
    #define FALL6 "M5", 5

    #define TC1   "P2", 15
    #define TC1_n "P7", 2
    #define TC2   "P3", 15
    #define TC2_n "P7", 4
    #define TC3   "P4", 15
    #define TC3_n "P7", 6
    #define TC4   "M2", 15
    #define TC4_n "P7", 8
    #define TC5   "M3", 15
    #define TC5_n "P7", 10
    #define TC6   "M4", 15
    #define TC6_n "P7", 12
    #define TC7   "P1", 15

    #define LEAD1   "N7", 2
    #define LEAD1_n "N7", 3
    #define LEAD2   "N7", 7
    #define LEAD2_n "N7", 6
    #define LEAD3   "N7", 10
    #define LEAD3_n "N7", 11
    #define LEAD4   "N7", 15
    #define LEAD4_n "N7", 14
    #define LEAD5   "N6", 2
    #define LEAD5_n "N6", 3
    #define LEAD6   "N6", 7
    #define LEAD6_n "N6", 6
    #define LEAD7   "E1", 5
    #define LEAD7_n "E1", 6

    #define X1   "F7", 12
    #define X2   "F7", 9
    #define X3   "F7", 8
    #define X4   "F7", 11
    #define X4_n "J8", 8

    #define GALLOP_A "F4", 11
    #define GALLOP_B "F4", 6

    #define HIT_TRIGGER_n "A4", 5

    #define HIT1_n "N5", 12
    #define HIT2_n "N5", 11
    #define HIT3_n "N5", 10
    #define HIT4_n "N5", 9
    #define HIT5_n "N5", 3
    #define HIT6_n "N5", 4
    
    #define GAME_RESET1_n "E5", 5
    #define GAME_RESET2_n "E6", 1
    #define GAME_RESET3_n "E6", 4
    #define BUG_TRIG_n    "D6", 6

    #define A   "N6", 10
    #define A_n "N6", 11
    #define B   "N6", 15
    #define C   "A4", 9

    #define T1  "A2", 14
    #define T2  "A2", 13

    #define ATTRACT   "F8", 6
    #define ATTRACT_n "D6", 4

    #define COIN  "CAP20", 2
    #define PLAY4 "F6", 6
    #define PLAY6 "F6", 8
    #define Q     "H8", 2
    #define Q_n   "H8", 4

    #define RAND     "H8", 10
        
    #define FINISH_LINE "B4", 6
    #define PICKET_LINE "B1", 15
    #define PICKET_n    "B3", 6

    #define HORSES      "J2", 4
    #define HORSES_n    "F3", 12
    
    /**************************************************************************
    * Layout - Page 1                                                         *
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    CONNECTION("B3", 8, "B4", 9)

    CONNECTION("VIDEO", 1, "B4", 8)
    CONNECTION("VIDEO", Video::HBLANK_PIN, HSYNC)
    CONNECTION("VIDEO", Video::VBLANK_PIN, VSYNC)



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
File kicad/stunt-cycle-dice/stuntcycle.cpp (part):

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	/**************************************************************************
		Lines
	**************************************************************************/	
	#define HF_CLOCK  "CLOCK", 1
	#define CLOCK  "N4", 9
	#define CLOCK_n  "N4", 8
	
	#define _1H  "M4", 14
	#define _2H  "M4", 13
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	#define _256H  "K4", 3
	#define _256H_n  "K4", 2
	
	#define HRESET_n  "J6", 6
	#define HRESET  "H6", 6

	#define _1V  "L3", 12
	#define _2V  "L3", 9
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	#define _256V  "K4", 5
	#define _256V_n  "K4", 6
	
	#define VRESET_n  "M3", 9
	#define VRESET  "M3", 8
	
	#define HSYNC  "J5", 1
	#define HSYNC_n  "J5", 4
	
	#define VSYNC  "J5", 10
	#define VSYNC_n  "J5", 13
	
	#define _32H_xor_256H  "J4", 6
	#define _128H_xor_256H  "J4", 8
	
	#define HSCORE_n  "H4", 8
	#define VSCORE_n  "H4", 12
	#define SCORE_WINDOW  "J3", 1
	
    #define PLAYER_CONTROL "H6", 8
    #define PLAYER_CONTROL_n "D5", 11

    #define RETURN_THROTTLE GND // TEMP
    #define RETURN_THROTTLE_n "K8", 2
    #define FREE_PLAY "F8", 6
    #define FREE_PLAY_n "F8", 5
    #define ATTRACT "D9", 8
    #define ATTRACT_n "D9", 9

	#define COMP_SCORE_n  "A5", 5
	#define SCORE1_n  "M7", 6
	#define SCORE2  "K6", 1
	
	#define ROAD_n  "H4", 6
	
	//#define FIXED_RAMP_ZONE  "D8", 8
	#define FIXED_RAMP_ZONE  "C58", 2
	#define FIXED_RAMP_ZONE_n  "H6", 4
	#define OBJECT_ZONE  "J7", 9
	#define OBJECT_ZONE_n  "J7", 8
	#define VRAMP  "N3", 8
    #define VRAMP_n "E3", 8 // Is this correct? Name not shown
	#define RAMPS  "L1", 4
    #define RAMPS_n "L1", 10

	#define H1  "C3", 14
	#define H2  "C3", 13
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	#define V3  "K1", 12
	#define V4  "K1", 11

    #define DIRECTION "M3", 5
    #define DIRECTION_n "M3", 6

    #define HWINDOW "E4", 12
    #define HWINDOW_DELAYED "A4", 5
    #define HCOUNTER_RESET_n "D5", 3

    #define VWINDOW "K2", 15
    #define VCOUNTER_RESET_n "L2", 6
				
    #define CYCLE_WINDOW "L6", 11

    #define CYCLE_RESET_n "N6", 9
    #define CYCLE_RESET "N6", 10
    #define CYCLE_RESET_A_n "K8", 4

    #define GRAVITY "L6", 8

    #define OBJECT_HIT_n "M7", 3

    #define JUMP "N9", 11
    #define JUMP_n "N9", 3

    #define FLIP "N7", 5
    #define FLIP_n "N7", 6

    #define GOOD_JUMP "K7", 5
    #define GOOD_JUMP_n "K7", 6
    #define BAD_JUMP "K7", 9
    #define BAD_JUMP_n "K7", 8

    #define MS1 "B2", 11
    #define MS2 "B2", 3
    #define MS3 "N7", 8

    #define CYCLE "D2", 8
    #define CYCLE_n "D2", 9

    #define R2 "M8", 2
    #define R3 "M8", 6
    #define R4 "C1", 11

    #define START "D9", 6
    #define START_n "D9", 5

	/**************************************************************************
		Layout
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    CONNECTION("N6", 9, "N6", 3)

    // Capacitor C13 used apparently to drive a ~1us low pulse
    // onto M6 pin 5 at the falling edge of FLIP TIMER.
    CONNECTION("N6", 6, "C13", 1)
    CONNECTION(VCC, "C13", 2)

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    CONNECTION("VIDEO", 1, "E3", 12)
    CONNECTION("VIDEO", 2, "E4", 6)
    
    CONNECTION("VIDEO", Video::HBLANK_PIN, HSYNC)
    CONNECTION("VIDEO", Video::VBLANK_PIN, VSYNC)

CIRCUIT_LAYOUT_END

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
